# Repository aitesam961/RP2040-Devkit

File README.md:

# RP2040-Devkit 
This is a development board embedding a very popular RP2040 Microcontroller developed by Raspberry Pi Foundation. The idea is to design a very basic set of hardware for people getting started with RP2040 who just need a custom Board other than RP2040 Pico or if they want to design their own.

The RP2040 is supported with both C/C++ and MicroPython cross-platform development environments, including easy access to runtime debugging. It has UF2 boot and floating-point routines baked into the chip. The built-in USB can act as both device and host. It has two symmetric cores and high internal bandwidth, making it useful for signal processing and video. While the chip has a large amount of internal RAM, the board includes an additional 16MB external QSPI flash chip to store program code.

More About RP2040 Could be found here: [RP2040](https://www.raspberrypi.com/documentation/microcontrollers/rp2040.html)

#### Some Highlights about RP2040 Before we go Ahead

## Features:
* [ ] RP2040 Processor
* [ ] Raspberry PI silicon MCU
* [ ] Capable of handling python Codes
* [ ] USB-C for power
* [ ] On-Board Serial Wire Debug
* [ ] GPIO pins extended to 2.54mm pitch Headers
* [ ] Convenient for soldering on Boards
* [ ] Easy To flash directly through VS or Arduino IDE
* [ ] Low Power consumption
* [ ] Cost effective design
* [ ] Small Size. Perfect for tight Fit projects

## What's Special About it!!

The RP2040 utilizes dual ARM Cortex-M0+ processors (up to 133MHz) and features:
- 264kB of embedded SRAM in six banks
- Six dedicated IO for SPI Flash (supporting XIP)

## Connectivity
- 30 multifunction GPIO
- Dedicated hardware for commonly used peripherals
- Programmable IO for extended peripheral support
- Four channel ADC with internal temperature sensor, 0.5 MSa/s, 12-bit conversion
- USB 1.1 Host/Device

> **Note:** The GPIO pins are muxed so you can reconfigure the pins for the digital interface of your choice! Check out the RP2040 datasheet for more information on the pins that are broken out on the board.

=== Software Development

https://datasheets.raspberrypi.com/pico/raspberry-pi-pico-c-sdk.pdf[Raspberry Pi Pico C/{cpp} SDK]:: Libraries and tools for C/C++ development on RP2040 microcontrollers

https://datasheets.raspberrypi.com/pico/raspberry-pi-pico-python-sdk.pdf[Raspberry Pi Pico Python SDK]:: A MicroPython environment for RP2040 microcontrollers

The API level Doxygen documentation for the Raspberry Pi Pico C/{cpp} SDK is also available https://rptl.io/pico-doxygen[as a micro-site].

## Contributions

Contributions are what make the open source community such an amazing place to learn, inspire, and create. Any contributions you make are **greatly appreciated**.

If you have a suggestion that would make this better, please fork the repo and create a pull request. You can also simply open an issue with the tag "enhancement".
Don't forget to give the project a star! Thanks again!

1. Fork the Project
2. Create your Feature Branch (`git checkout -b feature/AmazingFeature`)
3. Commit your Changes (`git commit -m 'Add some AmazingFeature'`)
4. Push to the Branch (`git push origin feature/AmazingFeature`)
5. Open a Pull Request

> [NOTE]
If you are building applications with the C/C++ SDK and targeting boards other than the Raspberry Pi Pico, you will need to pass `-DPICO_BOARD=boardname` to CMake. Here `boardname` is the name of your board, e.g. for the Adafruit Feather RP2040 you should pass `-DPICO_BOARD=adafruit_feather_rp2040`. See the https://github.com/raspberrypi/pico-sdk/tree/master/src/boards[`boards/` directory] in the Pico SDK, and the https://forums.raspberrypi.com/viewtopic.php?f=147&t=304393[forums], for more information.

For More Information, refer to The [Datasheet](https://datasheets.raspberrypi.com/pico/pico-datasheet.pdf)

## License

Distributed under the MIT License. See `LICENSE.txt` for more information.

<p align="right">(<a href="#top">back to top</a>)</p>

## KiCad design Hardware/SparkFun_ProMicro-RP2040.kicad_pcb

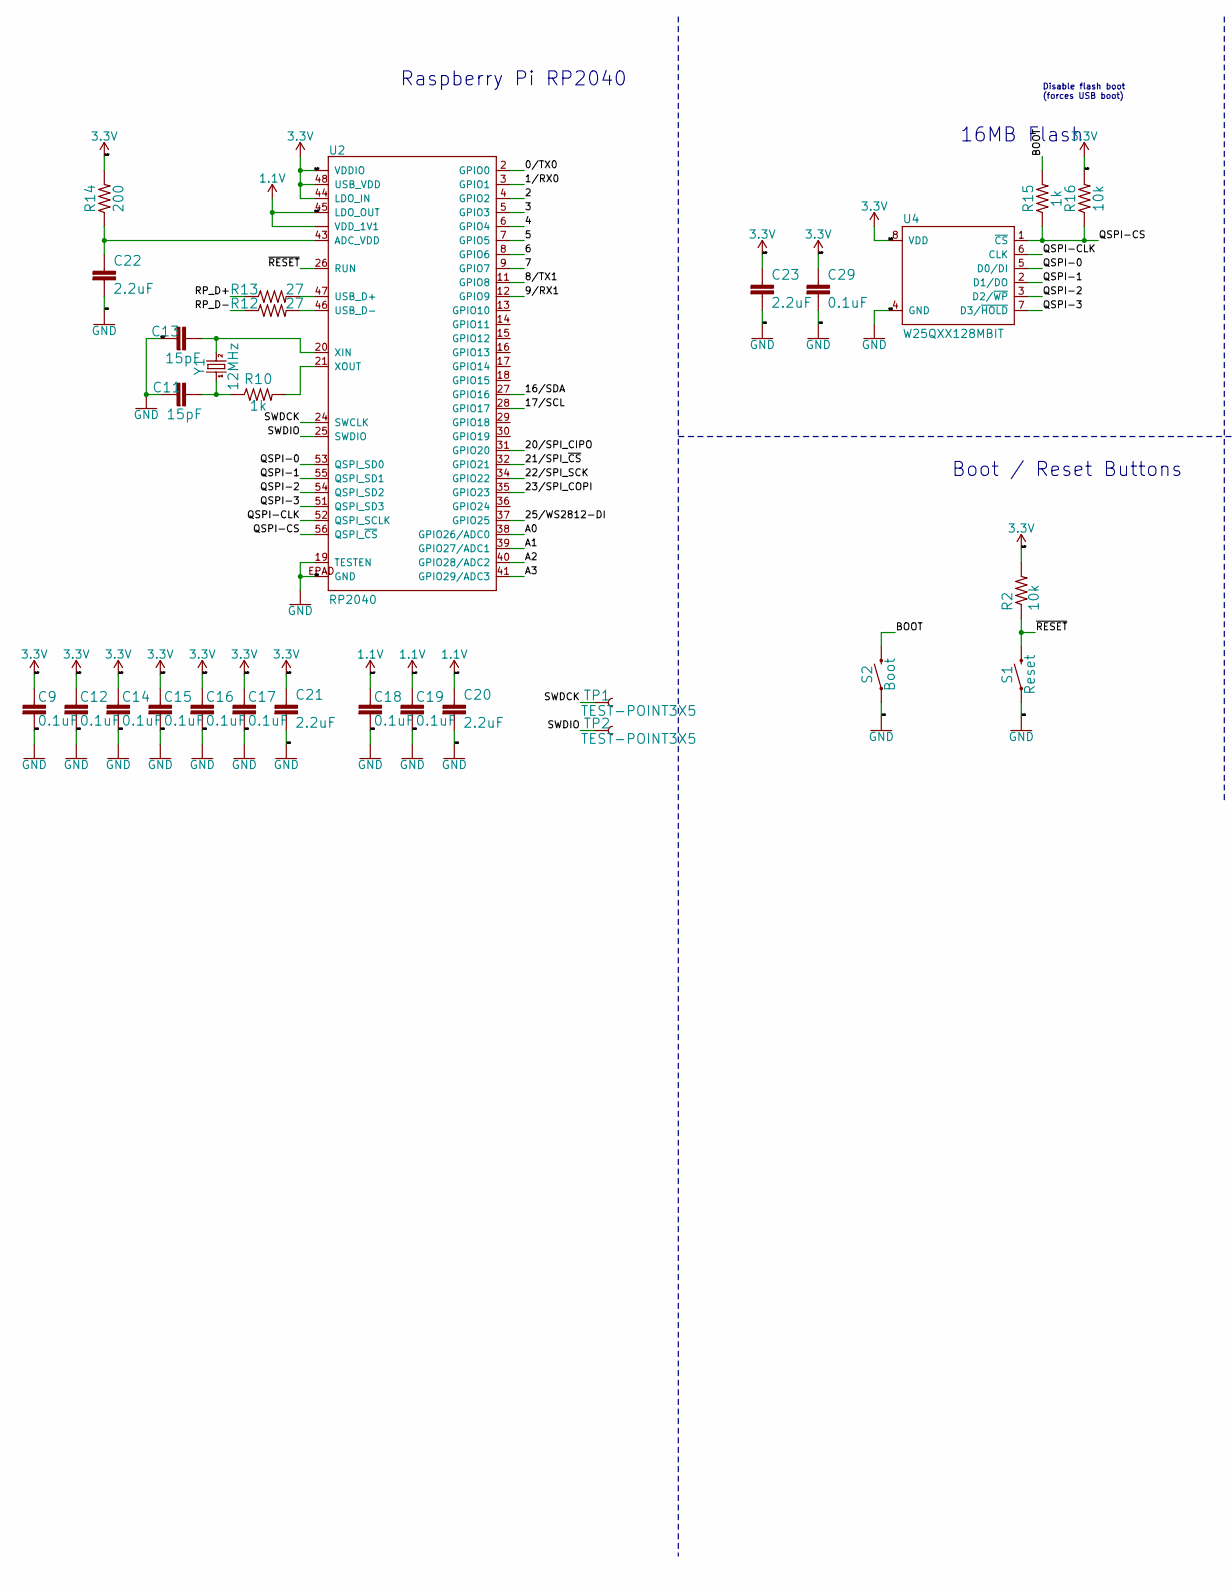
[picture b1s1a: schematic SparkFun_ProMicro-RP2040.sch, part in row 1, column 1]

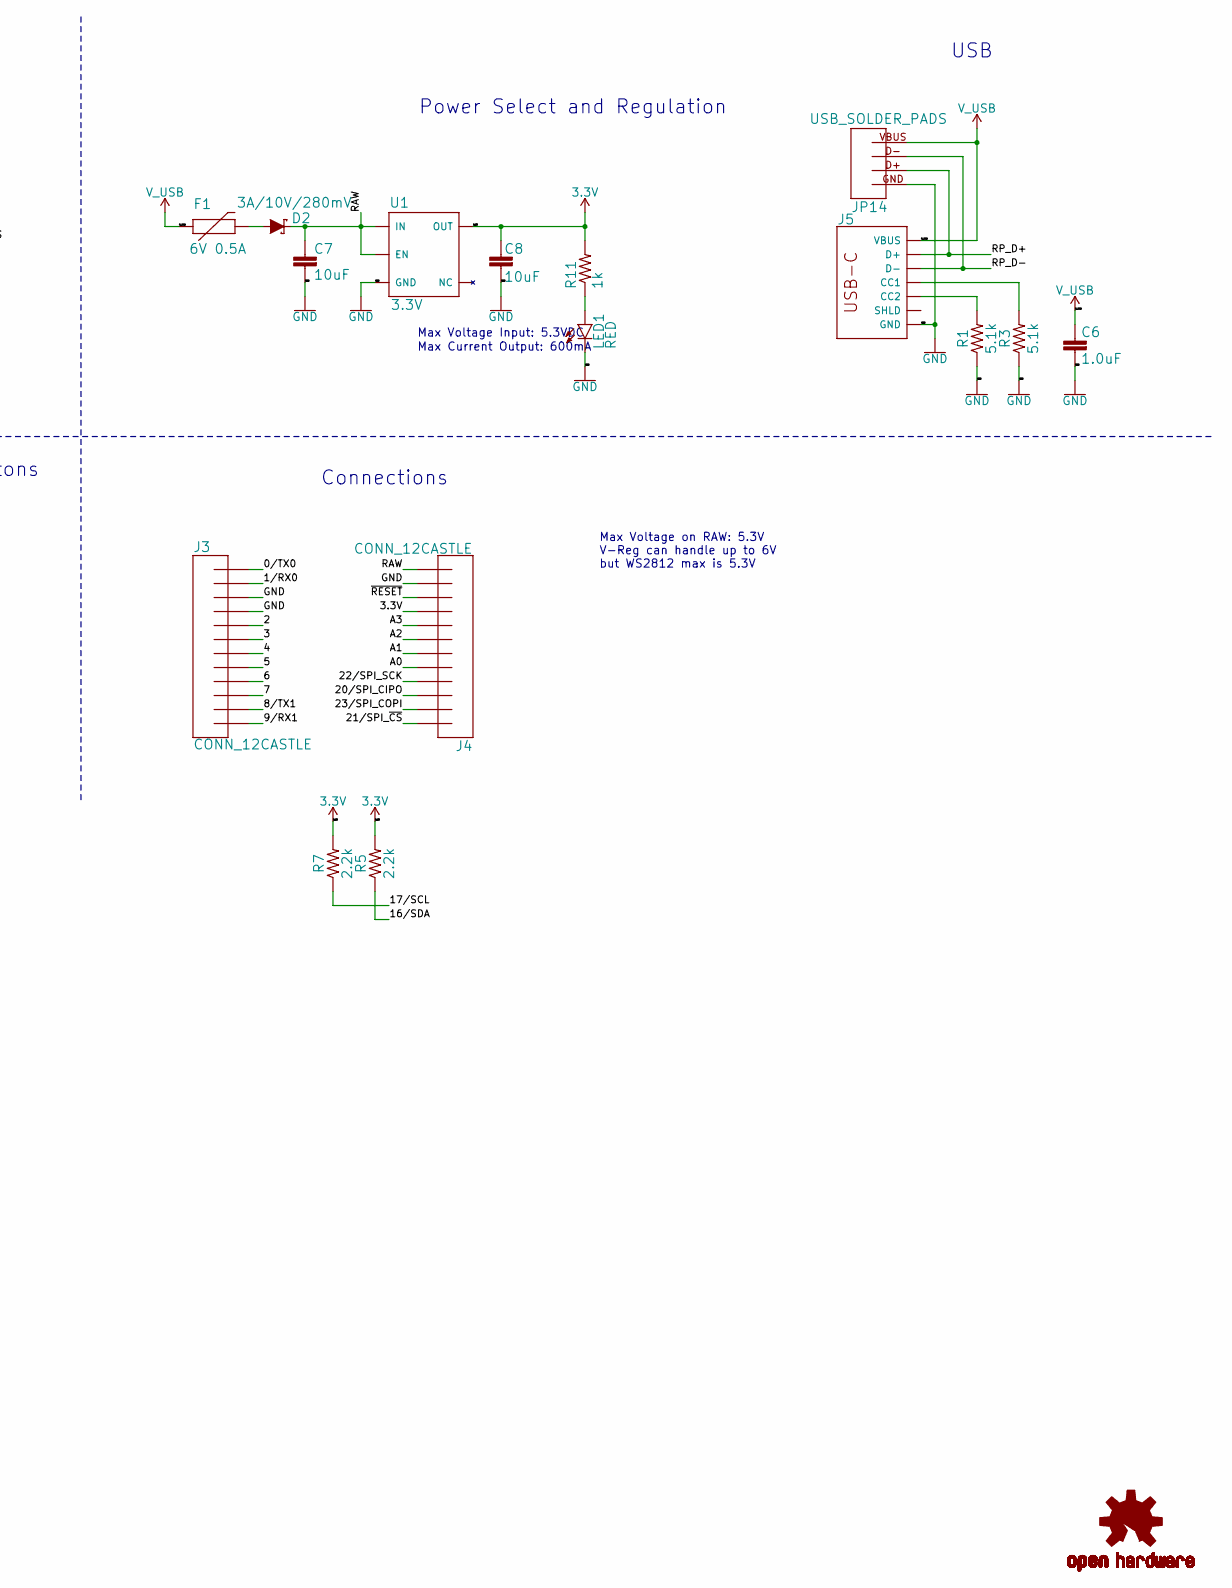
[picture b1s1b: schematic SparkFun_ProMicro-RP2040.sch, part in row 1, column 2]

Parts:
C6: 1.0uF; 0402-TIGHT
C7, C8: 10uF; 0402-TIGHT
C9, C12, C14, C15, C16, C17, C18, C19, C29: 0.1uF; 0402-TIGHT
C11, C13: 15pF; 0402-TIGHT
C20, C21, C22, C23: 2.2uF; 0402-TIGHT
D2: 3A/10V/280mV; SOD-323
F1: 6V 0.5A; 0805
J3, J4: CONN_12CASTLE; 1X12_CASTELLATED
J5: USB Female Type C Connector; USB-C-16P_4LAYER-PADS
JP14: USB_SOLDER_PADS; USB-SOLDER-PADS
LED1: RED; LED-0603
R1, R3: 5.1k; 0402-TIGHT
R2, R16: 10k; 0402-TIGHT
R5, R7: 2.2k; 0402-TIGHT
R10, R11, R15: 1k; 0402-TIGHT
R12, R13: 27; 0402-TIGHT
R14: 200; 0402-TIGHT
S1: Reset; TACTILE_SWITCH_SMD_4.6X2.8MM
S2: Boot; TACTILE_SWITCH_SMD_4.6X2.8MM
TP1, TP2: TEST-POINT3X5; PAD.03X.05
U1: 3.3V; SOT23-5
U2: RP2040; QFN-56
U4: W25QXX128MBIT; WSON-8-6X5-SKINNY_CENTERPAD
U$3: OSHW-LOGOMINI; OSHW-LOGO-MINI
Y1: 12MHz; CRYSTAL-SMD-2X2.5MM

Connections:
1.1V: C18.1, C19.1, C20.1, U2.23 (VDD_1V1), U2.45 (LDO_OUT), U2.50 (VDD_1V1)
3.3V: C8.2, C9.1, C12.1, C14.1, C15.1, C16.1, C17.1, C21.1, C23.1, C29.1, J4.4, J4.4B (4), R2.2, R5.2, R7.2, R11.2, R14.2, R16.2, U1.5 (OUT), U2.1 (VDDIO), U2.10 (VDDIO), U2.22 (VDDIO), U2.33 (VDDIO), U2.42 (VDDIO), U2.44 (LDO_IN), U2.48 (USB_VDD), U2.49 (VDDIO), U4.8 (VDD)
/0/TX0: J3.12, J3.12B (12), U2.2 (GPIO0)
/1/RX0: J3.11, J3.11B (11), U2.3 (GPIO1)
/2: J3.8, J3.8B (8), U2.4 (GPIO2)
/3: J3.7, J3.7B (7), U2.5 (GPIO3)
/4: J3.6, J3.6B (6), U2.6 (GPIO4)
/5: J3.5, J3.5B (5), U2.7 (GPIO5)
/6: J3.4, J3.4B (4), U2.8 (GPIO6)
/7: J3.3, J3.3B (3), U2.9 (GPIO7)
/8/TX1: J3.2, J3.2B (2), U2.11 (GPIO8)
/9/RX1: J3.1, J3.1B (1), U2.12 (GPIO9)
/16/SDA: R5.1, U2.27 (GPIO16)
/17/SCL: R7.1, U2.28 (GPIO17)
/20/SPI_CIPO: J4.10, J4.10B (10), U2.31 (GPIO20)
/21/SPI_~CS~: J4.12, J4.12B (12), U2.32 (GPIO21)
/22/SPI_SCK: J4.9, J4.9B (9), U2.34 (GPIO22)
/23/SPI_COPI: J4.11, J4.11B (11), U2.35 (GPIO23)
/A0: J4.8, J4.8B (8), U2.38 (GPIO26/ADC0)
/A1: J4.7, J4.7B (7), U2.39 (GPIO27/ADC1)
/A2: J4.6, J4.6B (6), U2.40 (GPIO28/ADC2)
/A3: J4.5, J4.5B (5), U2.41 (GPIO29/ADC3)
/BOOT: R15.2, S2.3 (2), S2.4 (2)
/QSPI-0: U2.53 (QSPI_SD0), U4.5 (D0/DI)
/QSPI-1: U2.55 (QSPI_SD1), U4.2 (D1/DO)
/QSPI-2: U2.54 (QSPI_SD2), U4.3 (D2/~WP~)
/QSPI-3: U2.51 (QSPI_SD3), U4.7 (D3/~HOLD~)
/QSPI-CLK: U2.52 (QSPI_SCLK), U4.6 (CLK)
/QSPI-CS: R15.1, R16.1, U2.56 (QSPI_~CS~), U4.1 (~CS~)
/RAW: C7.2, D2.C, J4.1, J4.1B (1), U1.1 (IN), U1.3 (EN)
/RP_D+: J5.A6 (D+), J5.B6 (D+), JP14.D+ (3), R13.1
/RP_D-: J5.A7 (D-), J5.B7 (D-), JP14.D- (2), R12.1
/SWDCK: TP1.P$1, U2.24 (SWCLK)
/SWDIO: TP2.P$1, U2.25 (SWDIO)
/~RESET~: J4.3, J4.3B (3), R2.1, S1.3 (2), S1.4 (2), U2.26 (RUN)
GND: C6.1, C7.1, C8.1, C9.2, C11.1, C12.2, C13.1, C14.2, C15.2, C16.2, C17.2, C18.2, C19.2, C20.2, C21.2, C22.2, C23.2, C29.2, J3.9, J3.9B (9), J3.10, J3.10B (10), J4.2, J4.2B (2), J5.GND, J5.GND2 (GND), JP14.GND (4), LED1.C, R1.1, R3.1, S1.1, S1.2 (1), S2.1, S2.2 (1), U1.2 (GND), U2.19 (TESTEN), U2.EPAD (GND), U4.4 (GND)
unnamed: C11.2, R10.1, Y1.P1 (1)
unnamed: C13.2, U2.20 (XIN), Y1.P3 (2)
unnamed: C22.1, R14.1, U2.43 (ADC_VDD)
unnamed: D2.A, F1.2
unnamed: J5.A5 (CC1), R3.2
unnamed: J5.B5 (CC2), R1.2
unnamed: J5.SHLD1 (SHLD), J5.SHLD2 (SHLD), J5.SHLD3 (SHLD), J5.SHLD4 (SHLD)
unnamed: LED1.A, R11.1
unnamed: R10.2, U2.21 (XOUT)
unnamed: R12.2, U2.46 (USB_D-)
unnamed: R13.2, U2.47 (USB_D+)
V_USB: C6.2, F1.1, J5.VBUS1 (VBUS), J5.VBUS2 (VBUS), JP14.VBUS (1)

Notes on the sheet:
Max Voltage Input: 5.3VDC
Max Current Output: 600mA
Raspberry Pi RP2040
16MB Flash
Disable flash boot (forces USB boot)
Power Select and Regulation
USB
Connections
Boot / Reset Buttons
Max Voltage on RAW: 5.3V V-Reg can handle up to 6V but WS2812 max is 5.3V

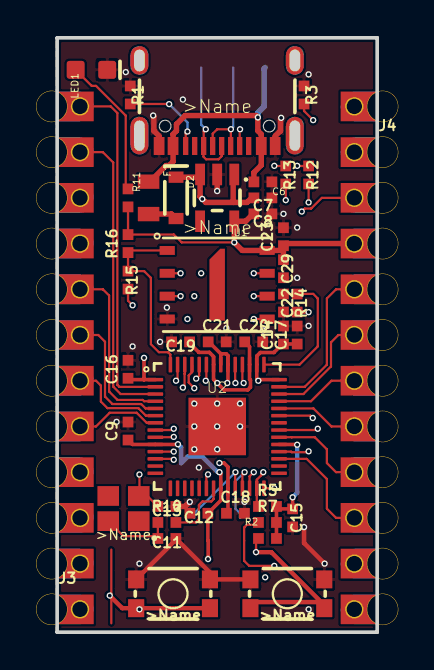
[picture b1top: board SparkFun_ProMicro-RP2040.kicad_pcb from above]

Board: 4 copper layers, 17.8 x 33.0 mm, 46 parts (0 on the bottom side), 48 nets.

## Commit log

2022-03-03 Create Documents
2022-03-03 Uploaded Gerber
